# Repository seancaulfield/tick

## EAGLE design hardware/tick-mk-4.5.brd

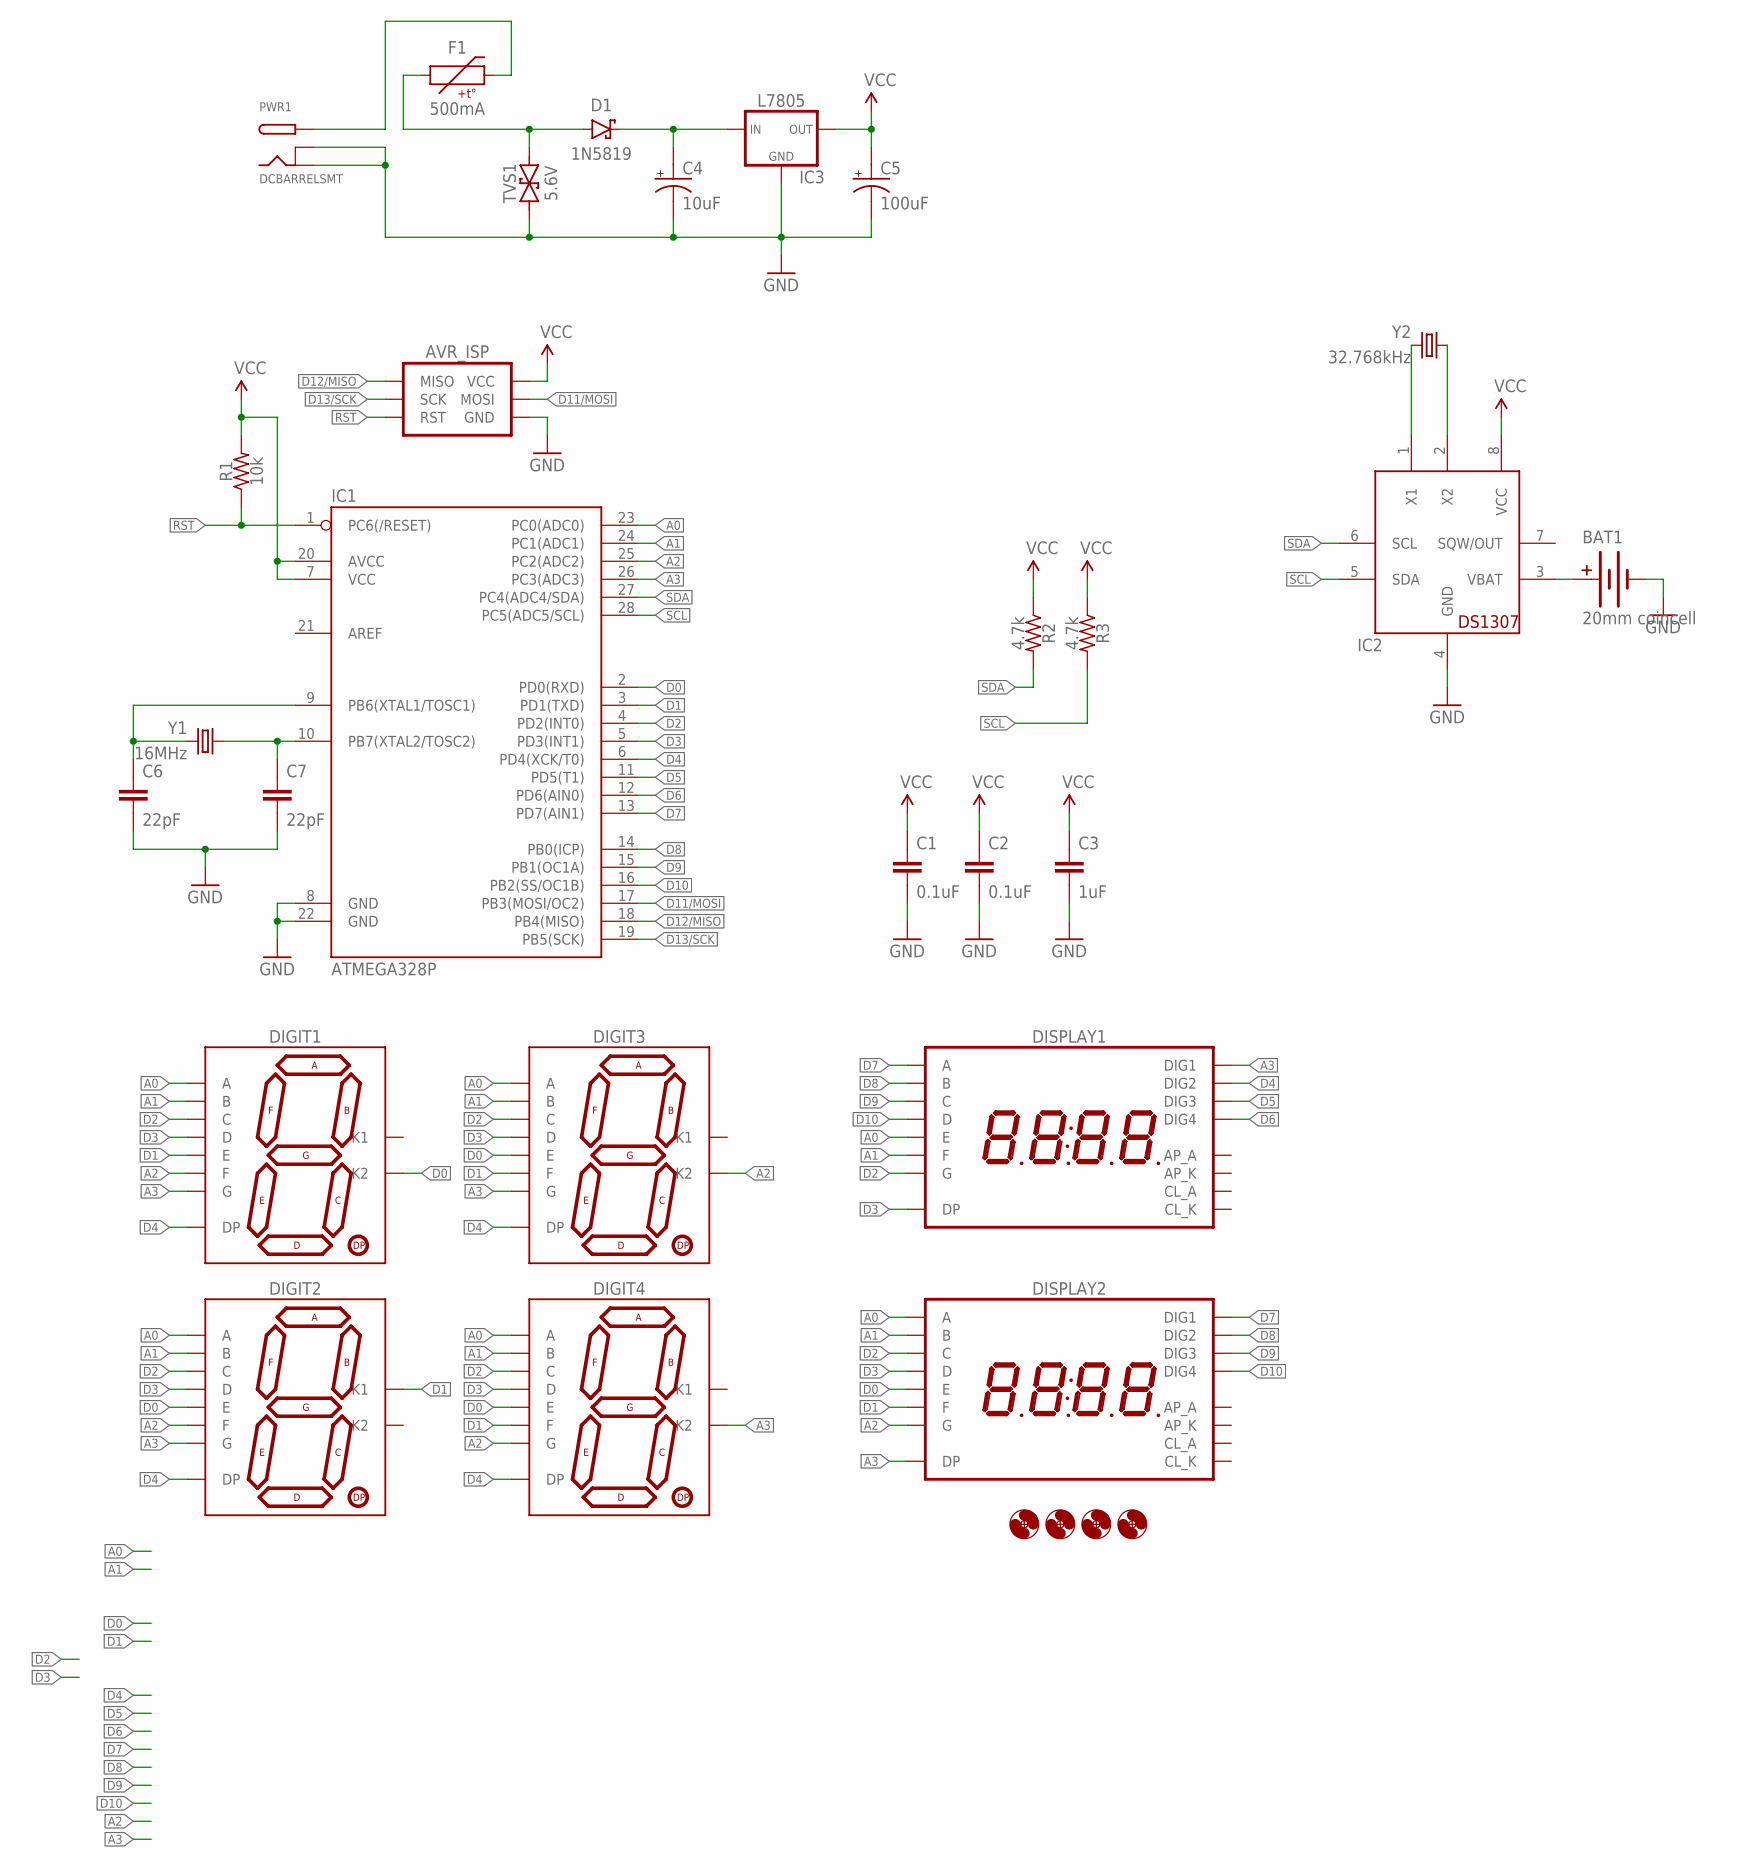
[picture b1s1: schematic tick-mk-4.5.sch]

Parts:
AVR_ISP: AVR_SPI_PRG_6PTH; 2X3
BAT1: 20mm coincell; BATTCON_20MM_MINE
C1, C2: 0.1uF; C025-024X044
C3: 1uF; C025-024X044
C4: 10uF; E2-5
C5: 100uF; E2,5-6
C6, C7: 22pF; C025-024X044
D1: 1N5819; DIODE-10.16MM
DIGIT1, DIGIT2, DIGIT3, DIGIT4: 7SEG_1DIGPTH-25.4MM-BARE; 7SEG_1DIG_25.4MM_NOSILK
DISPLAY1, DISPLAY2: 7SEG_4DIGIT_COLON_APOS; 7SEG_4DIG_10MM
F1: 500mA; PTC-PTH-5.08MM
H1, H2, H3, H4: HOLE#2; HOLE-#2
IC1: ATMEGA328P; DIL28-3
IC2: DS1307; DIL08
IC3: L7805; TO220-IGO-THERMPAD
PWR1: DCBARRELSMT; DCJACK_2MM_SMT
R1: 10k; RESISTOR-AXIAL-PTH-7.62MM
R2, R3: 4.7k; RESISTOR-AXIAL-PTH-7.62MM
TVS1: 5.6V; DO-41-TVS-BI-10.16MM
Y1: 16MHz; HC49U-V
Y2: 32.768kHz; TC26H

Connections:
A0: DIGIT1.7 (A), DIGIT2.7 (A), DIGIT3.7 (A), DIGIT4.7 (A), DISPLAY1.5 (E), DISPLAY2.14 (A), IC1.23 (PC0(ADC0))
A1: DIGIT1.6 (B), DIGIT2.6 (B), DIGIT3.6 (B), DIGIT4.6 (B), DISPLAY1.11 (F), DISPLAY2.16 (B), IC1.24 (PC1(ADC1))
A2: DIGIT1.9 (F), DIGIT2.9 (F), DIGIT3.8 (K2), DIGIT4.10 (G), DISPLAY2.15 (G), IC1.25 (PC2(ADC2))
A3: DIGIT1.10 (G), DIGIT2.10 (G), DIGIT3.10 (G), DIGIT4.8 (K2), DISPLAY1.1 (DIG1), DISPLAY2.7 (DP), IC1.26 (PC3(ADC3))
D0: DIGIT1.8 (K2), DIGIT2.1 (E), DIGIT3.1 (E), DIGIT4.1 (E), DISPLAY2.5 (E), IC1.2 (PD0(RXD))
D1: DIGIT1.1 (E), DIGIT2.3 (K1), DIGIT3.9 (F), DIGIT4.9 (F), DISPLAY2.11 (F), IC1.3 (PD1(TXD))
D2: DIGIT1.4 (C), DIGIT2.4 (C), DIGIT3.4 (C), DIGIT4.4 (C), DISPLAY1.15 (G), DISPLAY2.13 (C), IC1.4 (PD2(INT0))
D3: DIGIT1.2 (D), DIGIT2.2 (D), DIGIT3.2 (D), DIGIT4.2 (D), DISPLAY1.7 (DP), DISPLAY2.3 (D), IC1.5 (PD3(INT1))
D4: DIGIT1.5 (DP), DIGIT2.5 (DP), DIGIT3.5 (DP), DIGIT4.5 (DP), DISPLAY1.2 (DIG2), IC1.6 (PD4(XCK/T0))
D5: DISPLAY1.6 (DIG3), IC1.11 (PD5(T1))
D6: DISPLAY1.8 (DIG4), IC1.12 (PD6(AIN0))
D7: DISPLAY1.14 (A), DISPLAY2.1 (DIG1), IC1.13 (PD7(AIN1))
D8: DISPLAY1.16 (B), DISPLAY2.2 (DIG2), IC1.14 (PB0(ICP))
D9: DISPLAY1.13 (C), DISPLAY2.6 (DIG3), IC1.15 (PB1(OC1A))
D10: DISPLAY1.3 (D), DISPLAY2.8 (DIG4), IC1.16 (PB2(SS/OC1B))
D11/MOSI: AVR_ISP.4 (MOSI), IC1.17 (PB3(MOSI/OC2))
D12/MISO: AVR_ISP.1 (MISO), IC1.18 (PB4(MISO))
D13/SCK: AVR_ISP.3 (SCK), IC1.19 (PB5(SCK))
GND: AVR_ISP.6 (GND), BAT1.BOTTOM (-), C1.2, C2.2, C3.2, C4.-, C5.-, C6.2, C7.2, IC1.8 (GND), IC1.22 (GND), IC2.4 (GND), IC3.4 (GND), IC3.GND, PWR1.BRK, PWR1.GND, TVS1.P$1 (1)
unnamed: BAT1.TOP@1 (+), BAT1.TOP@2 (+), IC2.3 (VBAT)
unnamed: IC2.1 (X1), Y2.2
unnamed: IC2.2 (X2), Y2.1
unnamed: D1.A, F1.P$1 (1), TVS1.P$2 (2)
unnamed: C6.1, IC1.9 (PB6(XTAL1/TOSC1)), Y1.2
unnamed: C4.+, D1.C, IC3.IN
unnamed: C7.1, IC1.10 (PB7(XTAL2/TOSC2)), Y1.1
unnamed: F1.P$2 (2), PWR1.PWR@1 (PWR), PWR1.PWR@2 (PWR)
RST: AVR_ISP.5 (RST), IC1.1 (PC6(/RESET)), R1.P$1 (1)
SCL: IC1.28 (PC5(ADC5/SCL)), IC2.5 (SDA), R3.P$2 (2)
SDA: IC1.27 (PC4(ADC4/SDA)), IC2.6 (SCL), R2.P$2 (2)
VCC: AVR_ISP.2 (VCC), C1.1, C2.1, C3.1, C5.+, IC1.7 (VCC), IC1.20 (AVCC), IC2.8 (VCC), IC3.OUT, R1.P$2 (2), R2.P$1 (1), R3.P$1 (1)

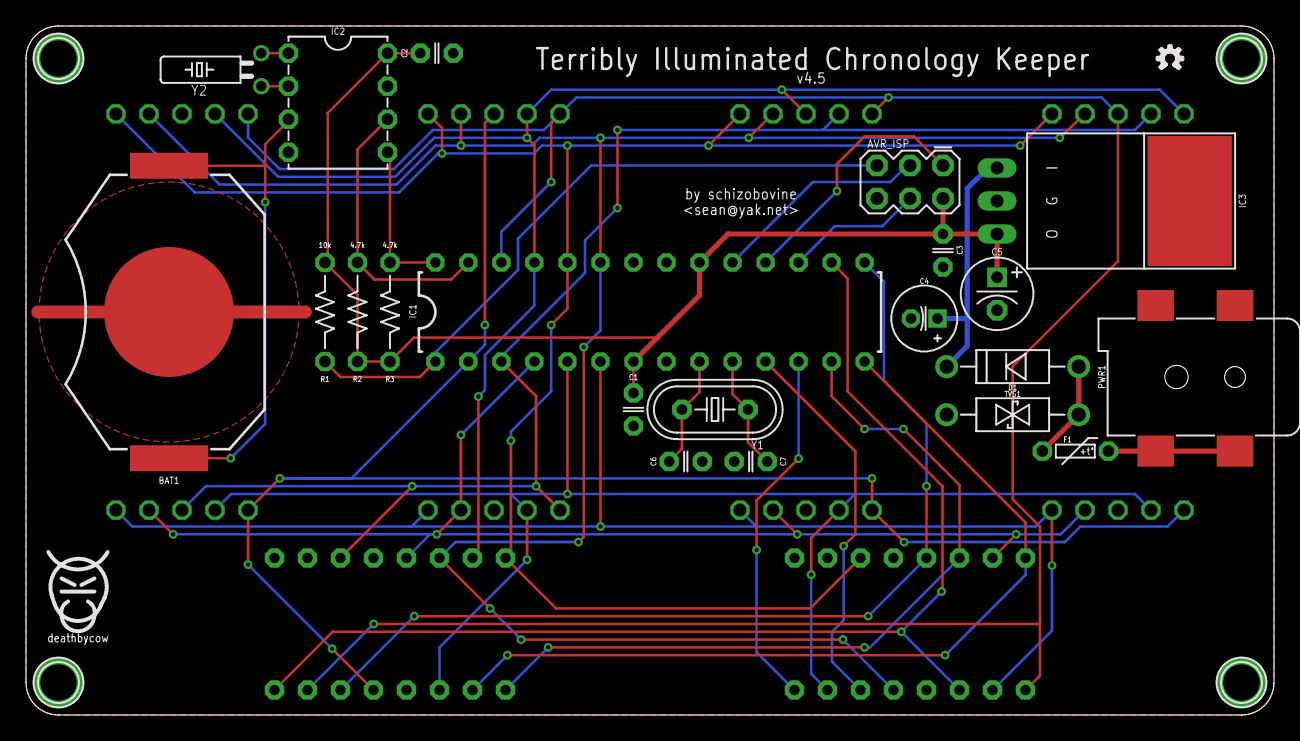
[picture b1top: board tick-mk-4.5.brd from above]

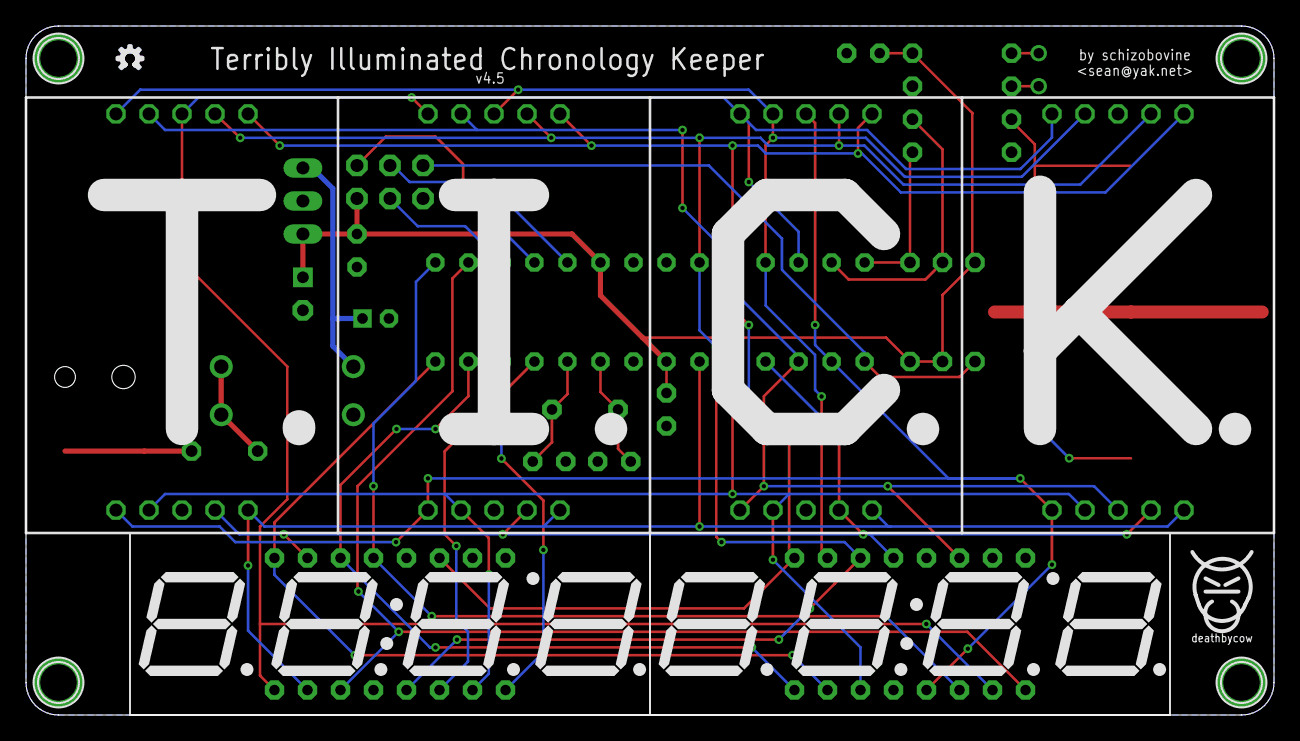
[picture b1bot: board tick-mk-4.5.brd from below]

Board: 2 copper layers, 96.0 x 53.0 mm, 35 parts (8 on the bottom side), 31 nets.

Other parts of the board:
U$1, U$4: COW_SMALL
U$6, U$7: OSHWLOGO_MINI

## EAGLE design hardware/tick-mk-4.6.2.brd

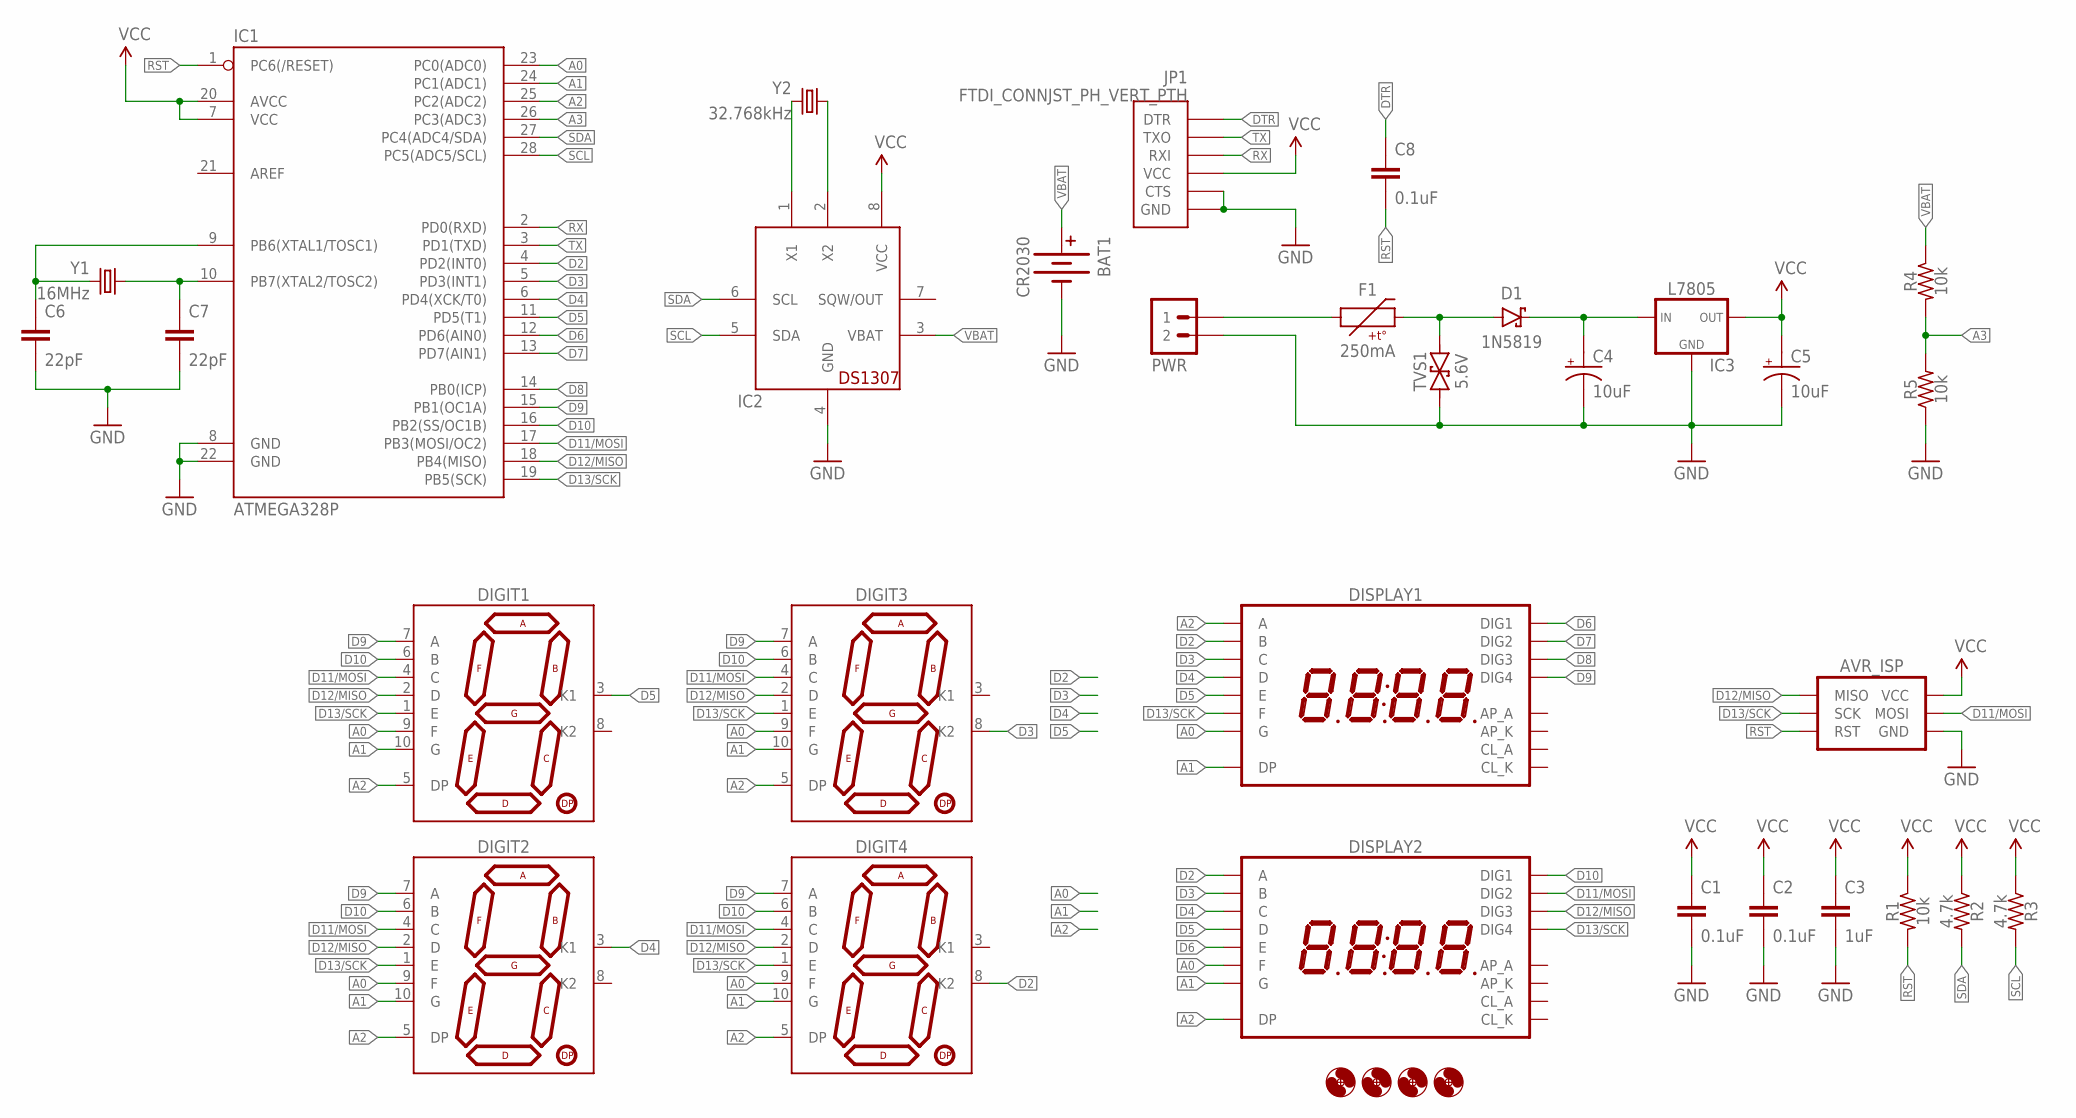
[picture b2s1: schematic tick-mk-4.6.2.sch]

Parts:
AVR_ISP: AVR_SPI_PRG_6PTH; 2X3
BAT1: CR2030; BATTCON_20MM_MINE
C1, C2, C8: 0.1uF; C025-024X044
C3: 1uF; C025-024X044
C4, C5: 10uF; E2-5
C6, C7: 22pF; C025-024X044
D1: 1N5819; DIODE-10.16MM
DIGIT1, DIGIT2, DIGIT3, DIGIT4: 7SEG_1DIGPTH-25.4MM-BARE; 7SEG_1DIG_25.4MM_NOSILK
DISPLAY1, DISPLAY2: 7SEG_4DIGIT_COLON_APOS; 7SEG_4DIG_10MM
F1: 250mA; PTC-PTH-5.08MM
H1, H2, H3, H4: HOLE#2; HOLE-#2
IC1: ATMEGA328P; DIL28-3
IC2: DS1307; DIL08
IC3: L7805; TO220-IGO-THERMPAD
JP1: FTDI_CONNJST_PH_VERT_PTH; FTDI_CONN_JST_PH_VERT_PTH
PWR: M02JST-PTH-VERT; JST-2-PH-VERT-PTH
R1: 10k; RESISTOR-AXIAL-PTH-7.62MM
R2, R3: 4.7k; RESISTOR-AXIAL-PTH-6.35MM
R4, R5: 10k; RESISTOR-AXIAL-PTH-6.35MM
TVS1: 5.6V; DO-41-TVS-BI-10.16MM
Y1: 16MHz; HC49U-V
Y2: 32.768kHz; TC26H

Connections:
A0: DIGIT1.9 (F), DIGIT2.9 (F), DIGIT3.9 (F), DIGIT4.9 (F), DISPLAY1.15 (G), DISPLAY2.11 (F), IC1.23 (PC0(ADC0))
A1: DIGIT1.10 (G), DIGIT2.10 (G), DIGIT3.10 (G), DIGIT4.10 (G), DISPLAY1.7 (DP), DISPLAY2.15 (G), IC1.24 (PC1(ADC1))
A2: DIGIT1.5 (DP), DIGIT2.5 (DP), DIGIT3.5 (DP), DIGIT4.5 (DP), DISPLAY1.14 (A), DISPLAY2.7 (DP), IC1.25 (PC2(ADC2))
A3: IC1.26 (PC3(ADC3)), R4.P$2 (2), R5.P$2 (2)
D2: DIGIT4.8 (K2), DISPLAY1.16 (B), DISPLAY2.14 (A), IC1.4 (PD2(INT0))
D3: DIGIT3.8 (K2), DISPLAY1.13 (C), DISPLAY2.16 (B), IC1.5 (PD3(INT1))
D4: DIGIT2.3 (K1), DISPLAY1.3 (D), DISPLAY2.13 (C), IC1.6 (PD4(XCK/T0))
D5: DIGIT1.3 (K1), DISPLAY1.5 (E), DISPLAY2.3 (D), IC1.11 (PD5(T1))
D6: DISPLAY1.1 (DIG1), DISPLAY2.5 (E), IC1.12 (PD6(AIN0))
D7: DISPLAY1.2 (DIG2), IC1.13 (PD7(AIN1))
D8: DISPLAY1.6 (DIG3), IC1.14 (PB0(ICP))
D9: DIGIT1.7 (A), DIGIT2.7 (A), DIGIT3.7 (A), DIGIT4.7 (A), DISPLAY1.8 (DIG4), IC1.15 (PB1(OC1A))
D10: DIGIT1.6 (B), DIGIT2.6 (B), DIGIT3.6 (B), DIGIT4.6 (B), DISPLAY2.1 (DIG1), IC1.16 (PB2(SS/OC1B))
D11/MOSI: AVR_ISP.4 (MOSI), DIGIT1.4 (C), DIGIT2.4 (C), DIGIT3.4 (C), DIGIT4.4 (C), DISPLAY2.2 (DIG2), IC1.17 (PB3(MOSI/OC2))
D12/MISO: AVR_ISP.1 (MISO), DIGIT1.2 (D), DIGIT2.2 (D), DIGIT3.2 (D), DIGIT4.2 (D), DISPLAY2.6 (DIG3), IC1.18 (PB4(MISO))
D13/SCK: AVR_ISP.3 (SCK), DIGIT1.1 (E), DIGIT2.1 (E), DIGIT3.1 (E), DIGIT4.1 (E), DISPLAY1.11 (F), DISPLAY2.8 (DIG4), IC1.19 (PB5(SCK))
DTR: C8.1, JP1.DTR
GND: AVR_ISP.6 (GND), BAT1.BOTTOM (-), C1.2, C2.2, C3.2, C4.-, C5.-, C6.2, C7.2, IC1.8 (GND), IC1.22 (GND), IC2.4 (GND), IC3.4 (GND), IC3.GND, JP1.CTS, JP1.GND, PWR.2, R5.P$1 (1), TVS1.P$1 (1)
unnamed: IC2.1 (X1), Y2.2
unnamed: IC2.2 (X2), Y2.1
unnamed: D1.A, F1.P$2 (2), TVS1.P$2 (2)
unnamed: C6.1, IC1.9 (PB6(XTAL1/TOSC1)), Y1.2
unnamed: F1.P$1 (1), PWR.1
unnamed: C4.+, D1.C, IC3.IN
unnamed: C7.1, IC1.10 (PB7(XTAL2/TOSC2)), Y1.1
RST: AVR_ISP.5 (RST), C8.2, IC1.1 (PC6(/RESET)), R1.P$2 (2)
RX: IC1.2 (PD0(RXD)), JP1.RXI
SCL: IC1.28 (PC5(ADC5/SCL)), IC2.5 (SDA), R3.P$2 (2)
SDA: IC1.27 (PC4(ADC4/SDA)), IC2.6 (SCL), R2.P$2 (2)
TX: IC1.3 (PD1(TXD)), JP1.TXO
VBAT: BAT1.TOP@1 (+), BAT1.TOP@2 (+), IC2.3 (VBAT), R4.P$1 (1)
VCC: AVR_ISP.2 (VCC), C1.1, C2.1, C3.1, C5.+, IC1.7 (VCC), IC1.20 (AVCC), IC2.8 (VCC), IC3.OUT, JP1.VCC, R1.P$1 (1), R2.P$1 (1), R3.P$1 (1)

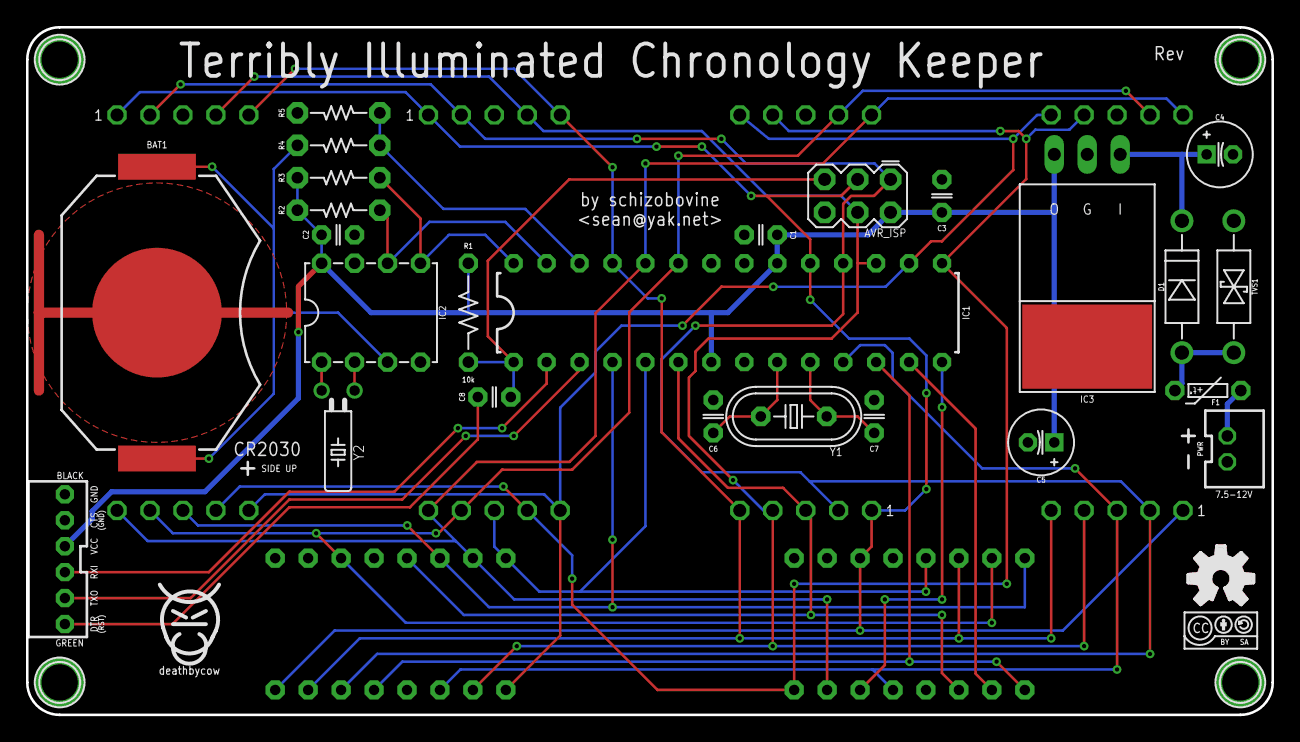
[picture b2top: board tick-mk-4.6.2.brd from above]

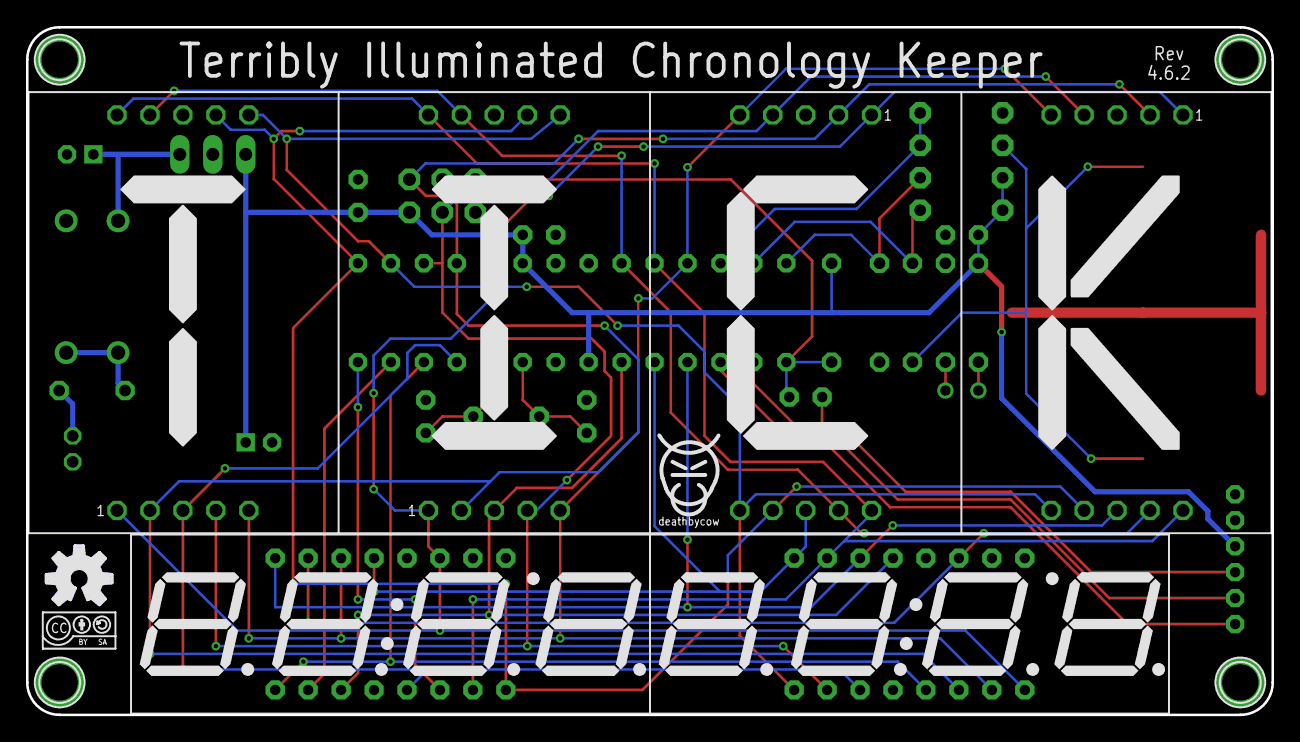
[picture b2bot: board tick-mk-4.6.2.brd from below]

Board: 2 copper layers, 96.0 x 53.0 mm, 42 parts (10 on the bottom side), 32 nets.

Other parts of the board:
U$1: TICK_SYMBOL
U$2, U$3: COW_SMALL
U$4, U$7: CC-BY-SA-4.0-NO-URL
U$5, U$6: OSHWLOGO_TOP_0.2
